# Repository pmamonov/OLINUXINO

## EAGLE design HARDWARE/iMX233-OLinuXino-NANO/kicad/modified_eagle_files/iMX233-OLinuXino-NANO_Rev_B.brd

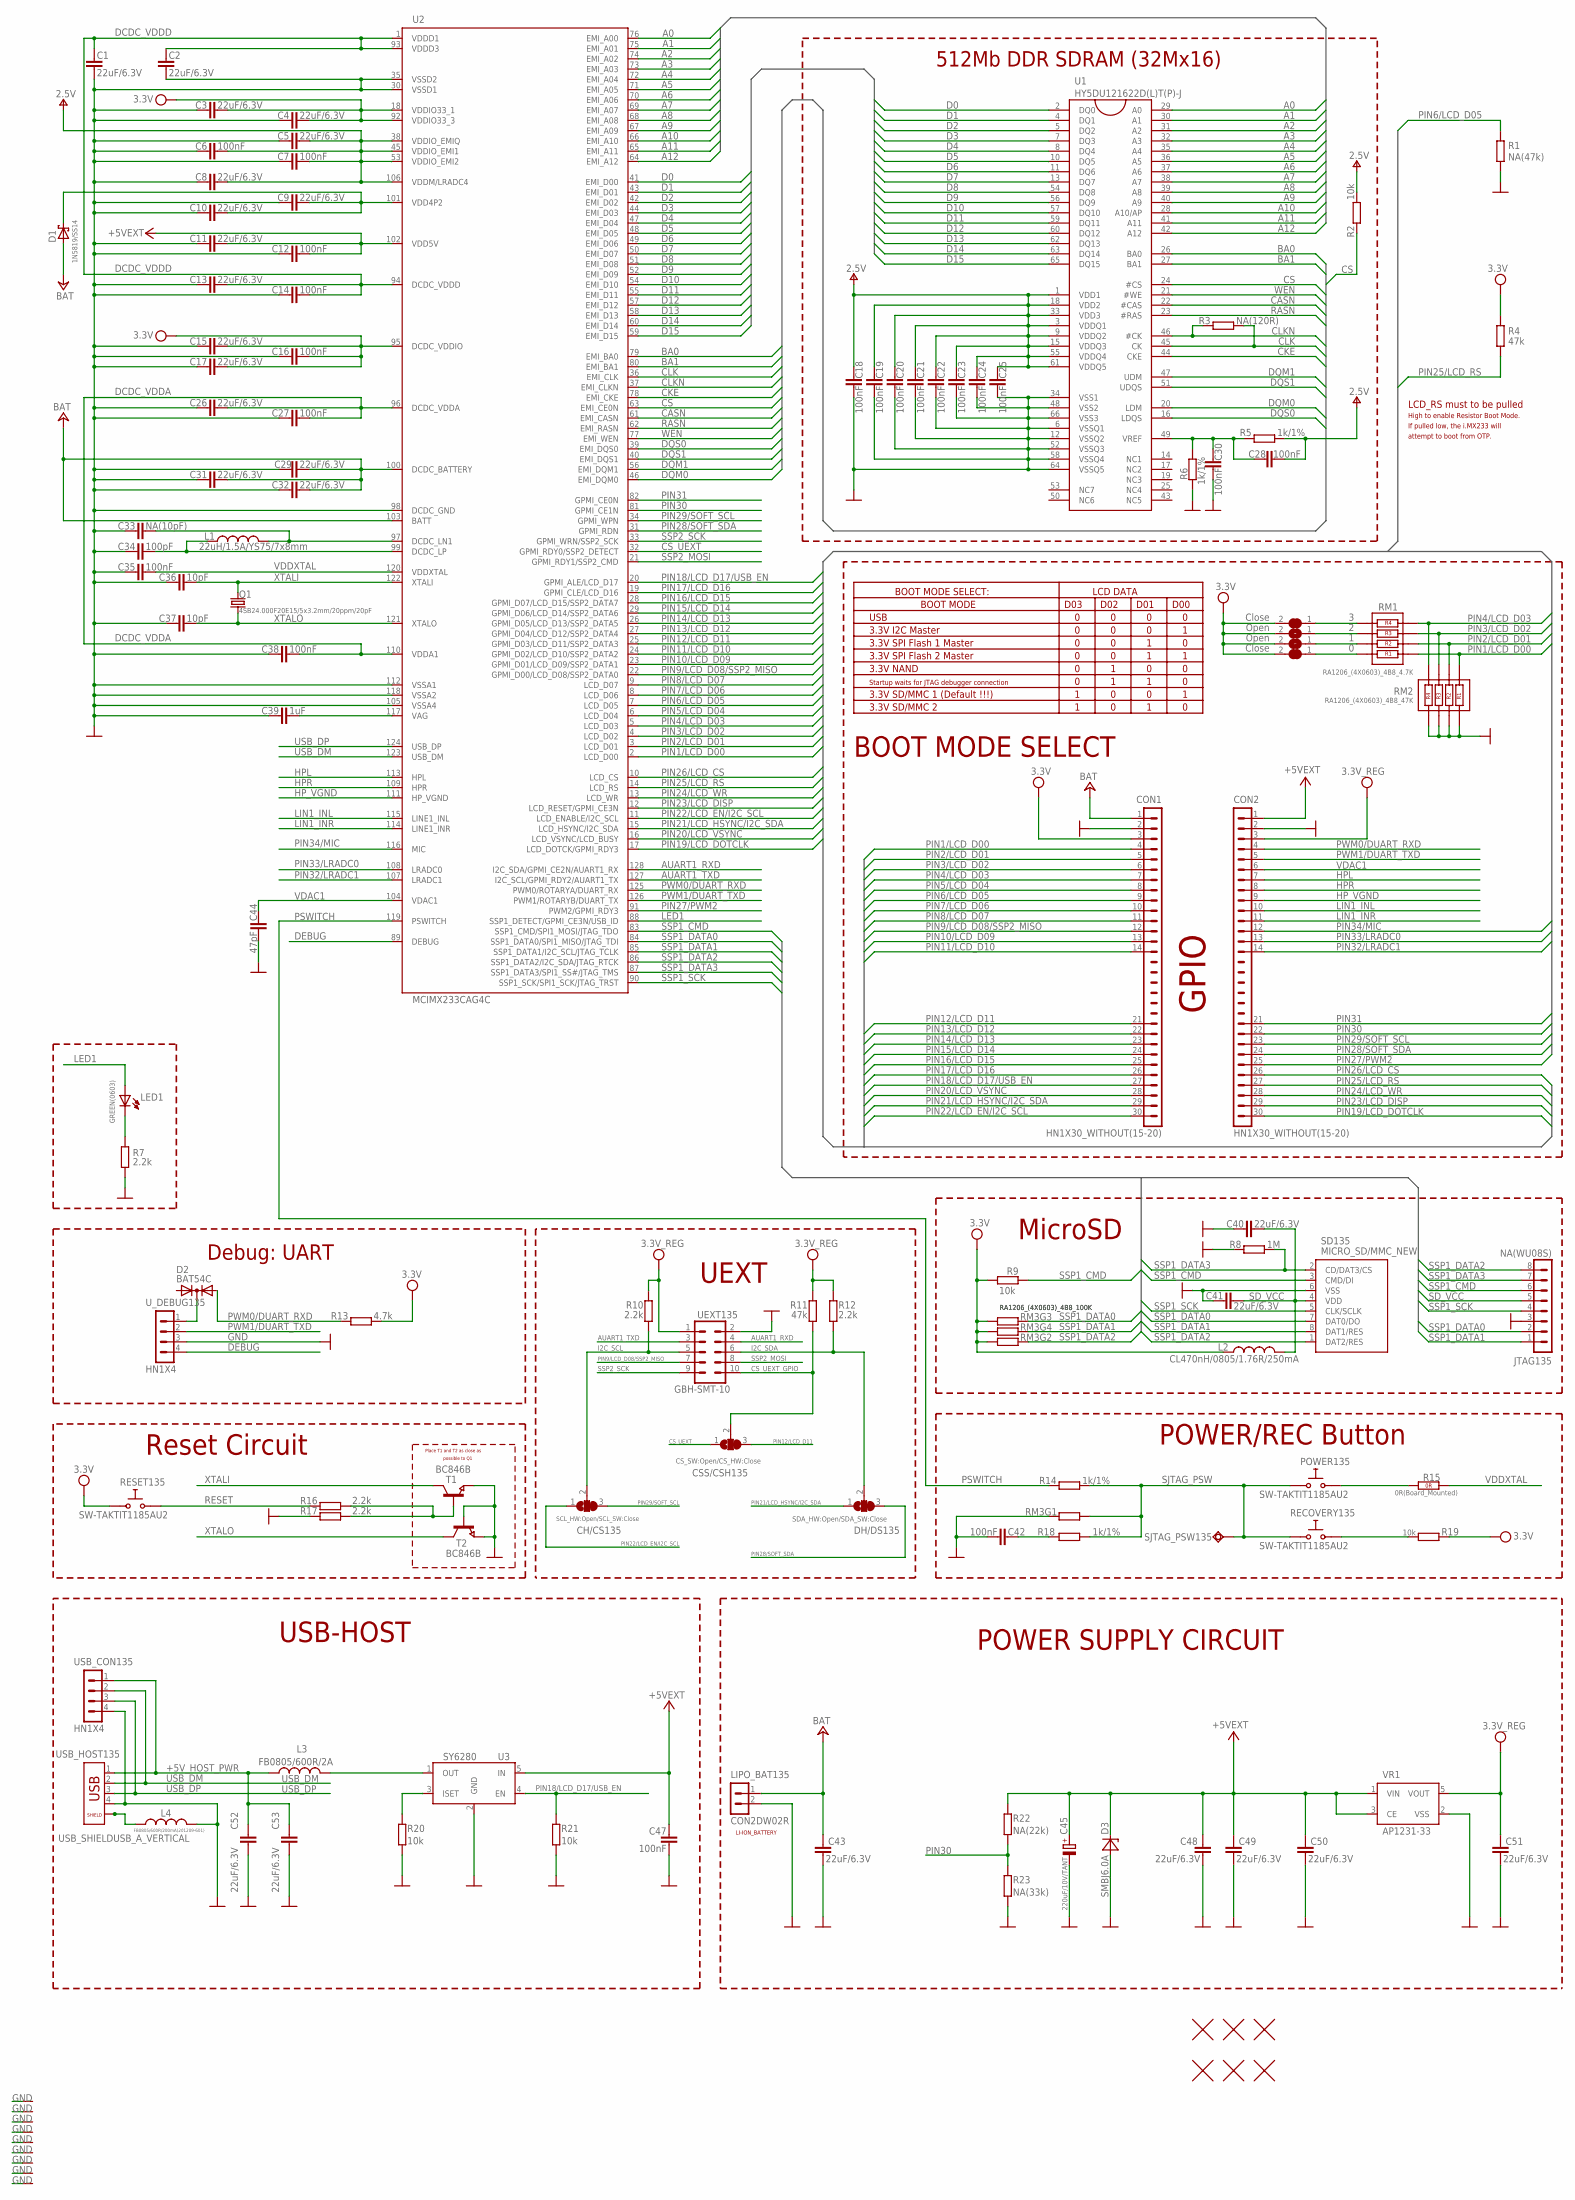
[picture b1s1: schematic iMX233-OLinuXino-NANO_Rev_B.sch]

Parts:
0, 3: Close; SJ_1_SMALLER
1, 2: Open; SJ_1_SMALLER
C1, C2, C3, C4, C5, C8, C9, C10, C11, C13, C15, C17, C26, C29, C31, C32, C40, C41, C43, C48, C49, C50, C51, C52, C53: 22uF/6.3V; C0603_DWS
C6, C7, C12, C14, C16, C18, C19, C20, C21, C22, C23, C24, C25, C27, C28, C30, C35, C38, C42: 100nF; C0402_TI
C33: NA(10pF); C0603_DWS
C34: 100pF; C0603_DWS
C36, C37: 10pF; C0603_DWS
C39: 1uF; C0603_DWS
C44: 47pF; C0603_DWS
C45: 220uF/10V/TANT; CT7343
C47: 100nF; C0603_DWS
CH/CS135: SCL_HW:Open/SCL_SW:Close; SJ_2_SMALLER
CON1, CON2: HN1X30_WITHOUT(15-20)
CSS/CSH135: CS_SW:Open/CS_HW:Close; SJ_2_SMALLER
D1: 1N5819/SS14; MLL-41
D2: BAT54C; SOT23C
D3: SMBJ6.0A; DO214AA
DH/DS135: SDA_HW:Open/SDA_SW:Close; SJ_2_SMALLER
JTAG135: NA(WU08S); WU08S
L1: 22uH/1.5A/YS75/7x8mm; L7078
L2: CL470nH/0805/1.76R/250mA; L0805_5MIL_DWS
L3: FB0805/600R/2A; L0805_5MIL_DWS
L4: FB0805/600R/200mA(201209-601); L0805_5MIL_DWS
LED1: GREEN(0603); LED-0603
LIPO_BAT135: CON2DW02R; DW02R
POWER135: SW-TAKTIT1185AU2; IT1185AU2
Q1: 4SB24.000F20E15/5x3.2mm/20ppm/20pF; HCX-4S
R1: NA(47k); R0603_5MIL_DWS
R2, R9, R19, R20, R21: 10k; R0603_5MIL_DWS
R3: NA(120R); R0603_5MIL_DWS
R4, R11: 47k; R0603_5MIL_DWS
R5, R6, R14, R18: 1k/1%; R0603_5MIL_DWS
R7, R10, R12, R16, R17: 2.2k; R0603_5MIL_DWS
R8: 1M; R0603_5MIL_DWS
R13: 4.7k; R0603_5MIL_DWS
R15: 0R(Board_Mounted); 0603_0R
R22: NA(22k); R0603_5MIL_DWS
R23: NA(33k); R0603_5MIL_DWS
RECOVERY135: SW-TAKTIT1185AU2; IT1185AU2
RESET135: SW-TAKTIT1185AU2; IT1185AU2
RM1: RA1206_(4X0603)_4B8_4.7K; R_MATRIX_4
RM2: RA1206_(4X0603)_4B8_47K; R_MATRIX_4
RM3: RA1206_(4X0603)_4B8_100K; R_MATRIX_4
SD135: MICRO_SD/MMC_NEW; TFR/C-MEM-CON
SJTAG_PSW135: TESTPAD40/70; TESTPAD
T1, T2: BC846B; SOT23
U1: HY5DU121622D(L)T(P)-J; 66TSOP-II
U2: MCIMX233CAG4C; TQFP128LD
U3: SY6280; SOT23-5
U$1, U$2, U$3, U$7, U$13, U$14: FIDUCIAL1X2; FIDUCIAL-1X2
UEXT135: GBH-SMT-10; ML10_S
USB_CON135: HN1X4
USB_HOST135: USB_SHIELDUSB_A_VERTICAL; USB_A_VERTICAL_PTH
U_DEBUG135: HN1X4
VP_0: VPDEV0; VPAC0
VP_1, VP_2, VP_3, VP_4, VP_5, VP_6, VP_7, VP_8: VPDEV1; VPAC1
VR1: AP1231-33; SOT-23-5

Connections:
+5V: C11.2, C12.2, C45.+, C47.1, C48.1, C49.1, C50.1, CON2.1, D3.C, R22.2, U2.102 (VDD5V), U3.5 (IN), VR1.1 (VIN), VR1.3 (CE)
+5V_HOST_PWR: C52.1, C53.1, L3.1, USB_CON135.1, USB_HOST135.1
+24V: C29.2, C31.2, C32.2, C43.1, CON1.1, D1.A, LIPO_BAT135.1, U2.100 (DCDC_BATTERY), U2.103 (BATT)
A0: U1.29 (A0), U2.76 (EMI_A00)
A1: U1.30 (A1), U2.75 (EMI_A01)
A2: U1.31 (A2), U2.74 (EMI_A02)
A3: U1.32 (A3), U2.73 (EMI_A03)
A4: U1.35 (A4), U2.72 (EMI_A04)
A5: U1.36 (A5), U2.71 (EMI_A05)
A6: U1.37 (A6), U2.70 (EMI_A06)
A7: U1.38 (A7), U2.69 (EMI_A07)
A8: U1.39 (A8), U2.68 (EMI_A08)
A9: U1.40 (A9), U2.67 (EMI_A09)
A10: U1.28 (A10/AP), U2.66 (EMI_A10)
A11: U1.41 (A11), U2.65 (EMI_A11)
A12: U1.42 (A12), U2.64 (EMI_A12)
AUART1_RXD: U2.128 (I2C_SDA/GPMI_CE2N/AUART1_RX), UEXT135.4
AUART1_TXD: U2.127 (I2C_SCL/GPMI_RDY2/AUART1_TX), UEXT135.3
BA0: U1.26 (BA0), U2.79 (EMI_BA0)
BA1: U1.27 (BA1), U2.80 (EMI_BA1)
CASN: U1.22 (#CAS), U2.61 (EMI_CASN)
CKE: U1.44 (CKE), U2.78 (EMI_CKE)
CLK: R3.2, U1.45 (CK), U2.36 (EMI_CLK)
CLKN: R3.1, U1.46 (#CK), U2.37 (EMI_CLKN)
CS: R2.1, U1.24 (#CS), U2.63 (EMI_CE0N)
CS_UEXT: CSS/CSH135.1, U2.32 (GPMI_RDY0/SSP2_DETECT)
CS_UEXT_GPIO: CSS/CSH135.2, R11.1, UEXT135.10
D0: U1.2 (DQ0), U2.41 (EMI_D00)
D1: U1.4 (DQ1), U2.43 (EMI_D01)
D2: U1.5 (DQ2), U2.42 (EMI_D02)
D3: U1.7 (DQ3), U2.44 (EMI_D03)
D4: U1.8 (DQ4), U2.47 (EMI_D04)
D5: U1.10 (DQ5), U2.48 (EMI_D05)
D6: U1.11 (DQ6), U2.49 (EMI_D06)
D7: U1.13 (DQ7), U2.50 (EMI_D07)
D8: U1.54 (DQ8), U2.51 (EMI_D08)
D9: U1.56 (DQ9), U2.52 (EMI_D09)
D10: U1.57 (DQ10), U2.54 (EMI_D10)
D11: U1.59 (DQ11), U2.55 (EMI_D11)
D12: U1.60 (DQ12), U2.57 (EMI_D12)
D13: U1.62 (DQ13), U2.58 (EMI_D13)
D14: U1.63 (DQ14), U2.60 (EMI_D14)
D15: U1.65 (DQ15), U2.59 (EMI_D15)
DCDC_VDDA: C26.2, C27.2, C38.2, U2.96 (DCDC_VDDA), U2.110 (VDDA1)
DCDC_VDDD: C1.2, C2.2, C13.2, C14.2, U2.1 (VDDD1), U2.93 (VDDD3), U2.94 (DCDC_VDDD)
DEBUG: U2.89 (DEBUG), U_DEBUG135.4
DQM0: U1.20 (LDM), U2.46 (EMI_DQM0)
DQM1: U1.47 (UDM), U2.56 (EMI_DQM1)
DQS0: U1.16 (LDQS), U2.39 (EMI_DQS0)
DQS1: U1.51 (UDQS), U2.40 (EMI_DQS1)
GND: C1.1, C2.1, C3.1, C4.1, C5.1, C6.1, C7.1, C8.1, C9.1, C10.1, C11.1, C12.1, C13.1, C14.1, C15.1, C16.1, C17.1, C18.1, C19.1, C20.1, C21.1, C22.1, C23.1, C24.1, C25.1, C26.1, C27.1, C29.1, C30.1, C31.1, C32.1, C33.1, C34.1, C35.1, C36.1, C37.1, C38.1, C39.1, C40.1, C41.1, C42.2, C43.2, C44.2, C45.-, C47.2, C48.2, C49.2, C50.2, C51.2, C52.2, C53.2, CON1.2, CON2.2, D3.A, JTAG135.3, L4.1, LIPO_BAT135.2, R1.1, R6.1, R7.1, R8.2, R17.2, R20.1, R21.1, R23.1, RM2.1.2, RM2.2.2, RM2.3.2, RM2.4.2, RM3.1.1 (1), SD135.6 (VSS), T1.2 (E), T2.1 (B), T2.2 (E), U1.6 (VSSQ1), U1.12 (VSSQ2), U1.34 (VSS1), U1.48 (VSS2), U1.52 (VSSQ3), U1.58 (VSSQ4), U1.64 (VSSQ5), U1.66 (VSS3), U2.30 (VSSD1), U2.35 (VSSD2), U2.98 (DCDC_GND), U2.105 (VSSA4), U2.112 (VSSA1), U2.118 (VSSA2), U3.2 (GND), UEXT135.2, USB_CON135.4, USB_HOST135.4, U_DEBUG135.3, VP_0.VP, VP_1.VP, VP_2.VP, VP_3.VP, VP_4.VP, VP_5.VP, VP_6.VP, VP_7.VP, VP_8.VP, VR1.2 (VSS)
HPL: CON2.7, U2.113 (HPL)
HPR: CON2.8, U2.109 (HPR)
HP_VGND: CON2.9, U2.111 (HP_VGND)
I2C_SCL: CH/CS135.2, R10.1, UEXT135.5
I2C_SDA: DH/DS135.2, R12.1, UEXT135.6
LED1: LED1.A, U2.88 (SSP1_DETECT/GPMI_CE3N/USB_ID)
LIN1_INL: CON2.10, U2.115 (LINE1_INL)
LIN1_INR: CON2.11, U2.114 (LINE1_INR)
unnamed: POWER135.1 (0), R15.1 (1.1)
unnamed: L3.2, U3.1 (OUT)
unnamed: R20.2, U3.3 (ISET)
unnamed: C28.2, C30.2, R5.1, R6.2, U1.49 (VREF)
unnamed: R19.1, RECOVERY135.1 (0)
unnamed: D2.3 (K), U_DEBUG135.1
unnamed: C33.2, L1.2, U2.97 (DCDC_LN1)
unnamed: C34.2, L1.1, U2.99 (DCDC_LP)
unnamed: C39.2, U2.117 (VAG)
unnamed: C42.1, R18.1
unnamed: LED1.C, R7.2
unnamed: R16.1, R17.1, T1.1 (B)
unnamed: 3.1, RM1.4.1
unnamed: 2.1, RM1.3.1
unnamed: 1.1, RM1.2.1
unnamed: 0.1, RM1.1.1
unnamed: L4.2, USB_HOST135.P$3 (5), USB_HOST135.P$4 (6)
PIN1/LCD_D00: CON1.4, RM1.1.2, RM2.1.1, U2.2 (LCD_D00)
PIN2/LCD_D01: CON1.5, RM1.2.2, RM2.2.1, U2.3 (LCD_D01)
PIN3/LCD_D02: CON1.6, RM1.3.2, RM2.3.1, U2.4 (LCD_D02)
PIN4/LCD_D03: CON1.7, RM1.4.2, RM2.4.1, U2.5 (LCD_D03)
PIN5/LCD_D04: CON1.8, U2.6 (LCD_D04)
PIN6/LCD_D05: CON1.9, R1.2, U2.7 (LCD_D05)
PIN7/LCD_D06: CON1.10, U2.8 (LCD_D06)
PIN8/LCD_D07: CON1.11, U2.9 (LCD_D07)
PIN9/LCD_D08/SSP2_MISO: CON1.12, U2.22 (GPMI_D00/LCD_D08/SSP2_DATA0), UEXT135.7
PIN10/LCD_D09: CON1.13, U2.23 (GPMI_D01/LCD_D09/SSP2_DATA1)
PIN11/LCD_D10: CON1.14, U2.24 (GPMI_D02/LCD_D10/SSP2_DATA2)
PIN12/LCD_D11: CON1.21, CSS/CSH135.3, U2.25 (GPMI_D03/LCD_D11/SSP2_DATA3)
PIN13/LCD_D12: CON1.22, U2.27 (GPMI_D04/LCD_D12/SSP2_DATA4)
PIN14/LCD_D13: CON1.23, U2.26 (GPMI_D05/LCD_D13/SSP2_DATA5)
PIN15/LCD_D14: CON1.24, U2.29 (GPMI_D06/LCD_D14/SSP2_DATA6)
PIN16/LCD_D15: CON1.25, U2.28 (GPMI_D07/LCD_D15/SSP2_DATA7)
PIN17/LCD_D16: CON1.26, U2.19 (GPMI_CLE/LCD_D16)
PIN18/LCD_D17/USB_EN: CON1.27, R21.2, U2.20 (GPMI_ALE/LCD_D17), U3.4 (EN)
PIN19/LCD_DOTCLK: CON2.30, U2.17 (LCD_DOTCK/GPMI_RDY3)
PIN20/LCD_VSYNC: CON1.28, U2.16 (LCD_VSYNC/LCD_BUSY)
PIN21/LCD_HSYNC/I2C_SDA: CON1.29, DH/DS135.1, U2.15 (LCD_HSYNC/I2C_SDA)
PIN22/LCD_EN/I2C_SCL: CH/CS135.1, CON1.30, U2.11 (LCD_ENABLE/I2C_SCL)
PIN23/LCD_DISP: CON2.29, U2.12 (LCD_RESET/GPMI_CE3N)
PIN24/LCD_WR: CON2.28, U2.13 (LCD_WR)
PIN25/LCD_RS: CON2.27, R4.2, U2.14 (LCD_RS)
PIN26/LCD_CS: CON2.26, U2.10 (LCD_CS)
PIN27/PWM2: CON2.25, U2.91 (PWM2/GPMI_RDY3)
PIN28/SOFT_SDA: CON2.24, DH/DS135.3, U2.31 (GPMI_RDN)
PIN29/SOFT_SCL: CH/CS135.3, CON2.23, U2.34 (GPMI_WPN)
PIN30: CON2.22, R22.1, R23.2, U2.81 (GPMI_CE1N)
PIN31: CON2.21, U2.82 (GPMI_CE0N)
PIN32/LRADC1: CON2.14, U2.107 (LRADC1)
PIN33/LRADC0: CON2.13, U2.108 (LRADC0)
PIN34/MIC: CON2.12, U2.116 (MIC)
PSWITCH: R14.1, U2.119 (PSWITCH)
PWM0/DUART_RXD: CON2.4, D2.2 (A2), R13.2, U2.125 (PWM0/ROTARYA/DUART_RX)
PWM1/DUART_TXD: CON2.5, U2.126 (PWM1/ROTARYB/DUART_TX), U_DEBUG135.2
RASN: U1.23 (#RAS), U2.62 (EMI_RASN)
RESET: R16.2, RESET135.1 (0)
SD_VCC: C40.2, C41.2, JTAG135.5, L2.2, SD135.4 (VDD)
SJTAG_PSW: POWER135.2 (1), R14.2, R18.2, RECOVERY135.2 (1), RM3.1.2 (2), SJTAG_PSW135.P$1
SSP1_CMD: JTAG135.6, R9.1, SD135.3 (CMD/DI), U2.83 (SSP1_CMD/SPI1_MOSI/JTAG_TDO)
SSP1_DATA0: JTAG135.2, RM3.3.2 (2), SD135.7 (DAT0/DO), U2.84 (SSP1_DATA0/SPI1_MISO/JTAG_TDI)
SSP1_DATA1: JTAG135.1, RM3.4.2 (2), SD135.8 (DAT1/RES), U2.85 (SSP1_DATA1/I2C_SCL/JTAG_TCLK)
SSP1_DATA2: JTAG135.8, RM3.2.2 (2), SD135.1 (DAT2/RES), U2.86 (SSP1_DATA2/I2C_SDA/JTAG_RTCK)
SSP1_DATA3: JTAG135.7, R8.1, SD135.2 (CD/DAT3/CS), U2.87 (SSP1_DATA3/SPI1_SS#/JTAG_TMS)
SSP1_SCK: JTAG135.4, SD135.5 (CLK/SCLK), U2.90 (SSP1_SCK/SPI1_SCK/JTAG_TRST)
SSP2_MOSI: U2.21 (GPMI_RDY1/SSP2_CMD), UEXT135.8
SSP2_SCK: U2.33 (GPMI_WRN/SSP2_SCK), UEXT135.9
USB_DM: U2.123 (USB_DM), USB_CON135.2, USB_HOST135.2
USB_DP: U2.124 (USB_DP), USB_CON135.3, USB_HOST135.3
V+: C5.2, C6.2, C7.2, C8.2, C18.2, C19.2, C20.2, C21.2, C22.2, C23.2, C24.2, C25.2, C28.1, R2.2, R5.2, U1.1 (VDD1), U1.3 (VDDQ1), U1.9 (VDDQ2), U1.15 (VDDQ3), U1.18 (VDD2), U1.33 (VDD3), U1.55 (VDDQ4), U1.61 (VDDQ5), U2.38 (VDDIO_EMIQ), U2.45 (VDDIO_EMI1), U2.53 (VDDIO_EMI2), U2.106 (VDDM/LRADC4)
VCC: 0.2, 1.2, 2.2, 3.2, C3.2, C4.2, C15.2, C16.2, C17.2, CON1.3, L2.1, R4.1, R9.2, R13.1, R19.2, RESET135.2 (1), RM3.2.1 (1), RM3.3.1 (1), RM3.4.1 (1), U2.18 (VDDIO33_1), U2.92 (VDDIO33_3), U2.95 (DCDC_VDDIO)
VDAC1: C44.1, CON2.6, U2.104 (VDAC1)
VDD4P2: C9.2, C10.2, D1.K (C), U2.101 (VDD4P2)
VDDXTAL: C35.2, R15.2 (1.2), U2.120 (VDDXTAL)
VPP: C51.1, CON2.3, R10.2, R11.2, R12.2, UEXT135.1, VR1.5 (VOUT)
WEN: U1.21 (#WE), U2.77 (EMI_WEN)
XTALI: C36.2, Q1.2, T1.3 (C), U2.122 (XTALI)
XTALO: C37.2, Q1.1, T2.3 (C), U2.121 (XTALO)

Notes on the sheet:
POWER SUPPLY CIRCUIT
Place T1 and T2 as close as
possible to Q1
Reset Circuit
512Mb DDR SDRAM (32Mx16)
MicroSD
POWER/REC Button
BOOT MODE SELECT
BOOT MODE SELECT:
LCD DATA
BOOT MODE
D03
D02
D01
D00
USB
3.3V I2C Master
3.3V SPI Flash 1 Master
3.3V SPI Flash 2 Master
3.3V NAND
Startup waits for JTAG debugger connection
3.3V SD/MMC 1 (Default !!!)
3.3V SD/MMC 2
LCD_RS must to be pulled
High to enable Resistor Boot Mode.
If pulled low, the i.MX233 will
attempt to boot from OTP.
GPIO
Debug: UART
UEXT
USB-HOST
LI-ION_BATTERY

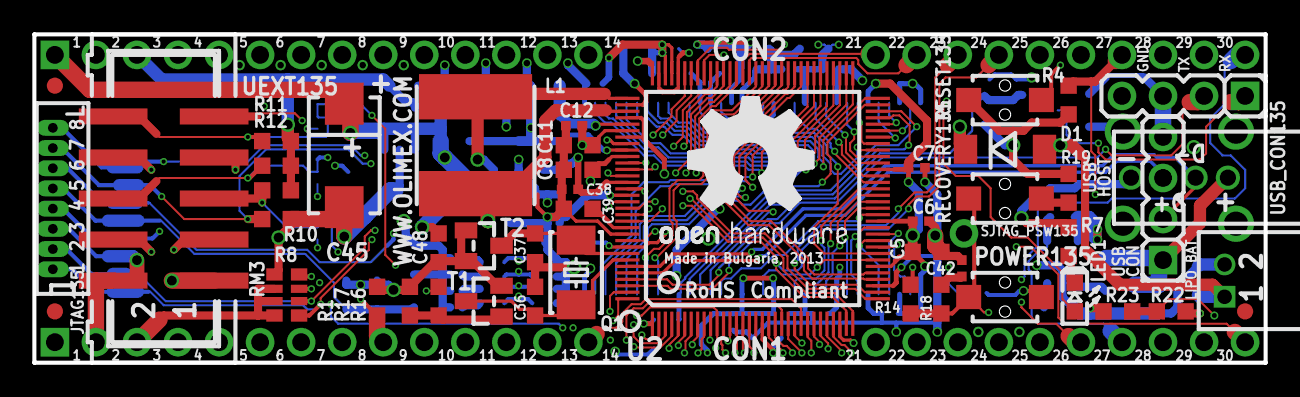
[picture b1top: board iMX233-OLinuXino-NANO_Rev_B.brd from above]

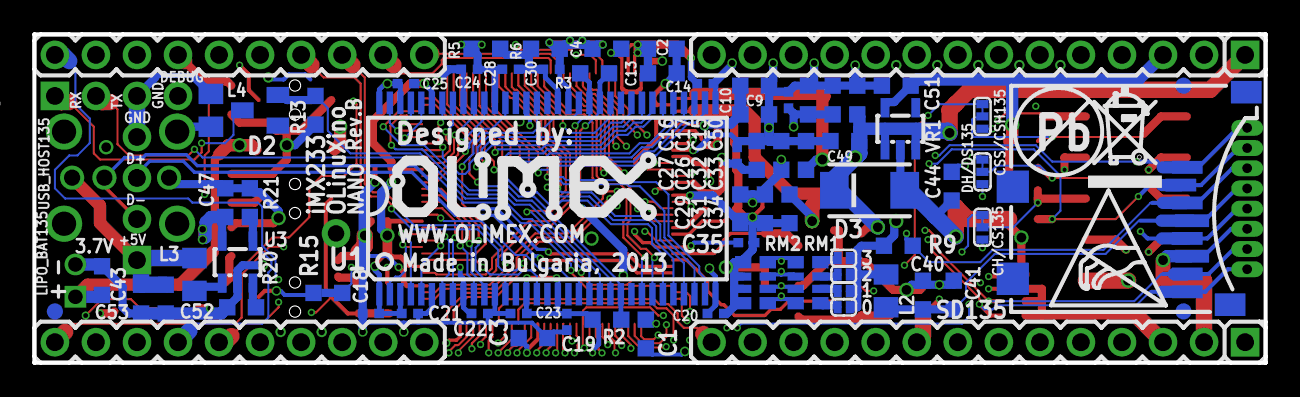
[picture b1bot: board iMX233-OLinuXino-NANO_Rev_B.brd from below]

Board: 6 copper layers, 76.2 x 20.3 mm, 133 parts (75 on the bottom side), 136 nets.

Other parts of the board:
U$4: ESD_SYMBOL
U$6: RECYCLE_BIN1/8
U$8: OLIMEX1_V
U$15: PB
U$18: LOGO-OPENHARDWARE_8X8

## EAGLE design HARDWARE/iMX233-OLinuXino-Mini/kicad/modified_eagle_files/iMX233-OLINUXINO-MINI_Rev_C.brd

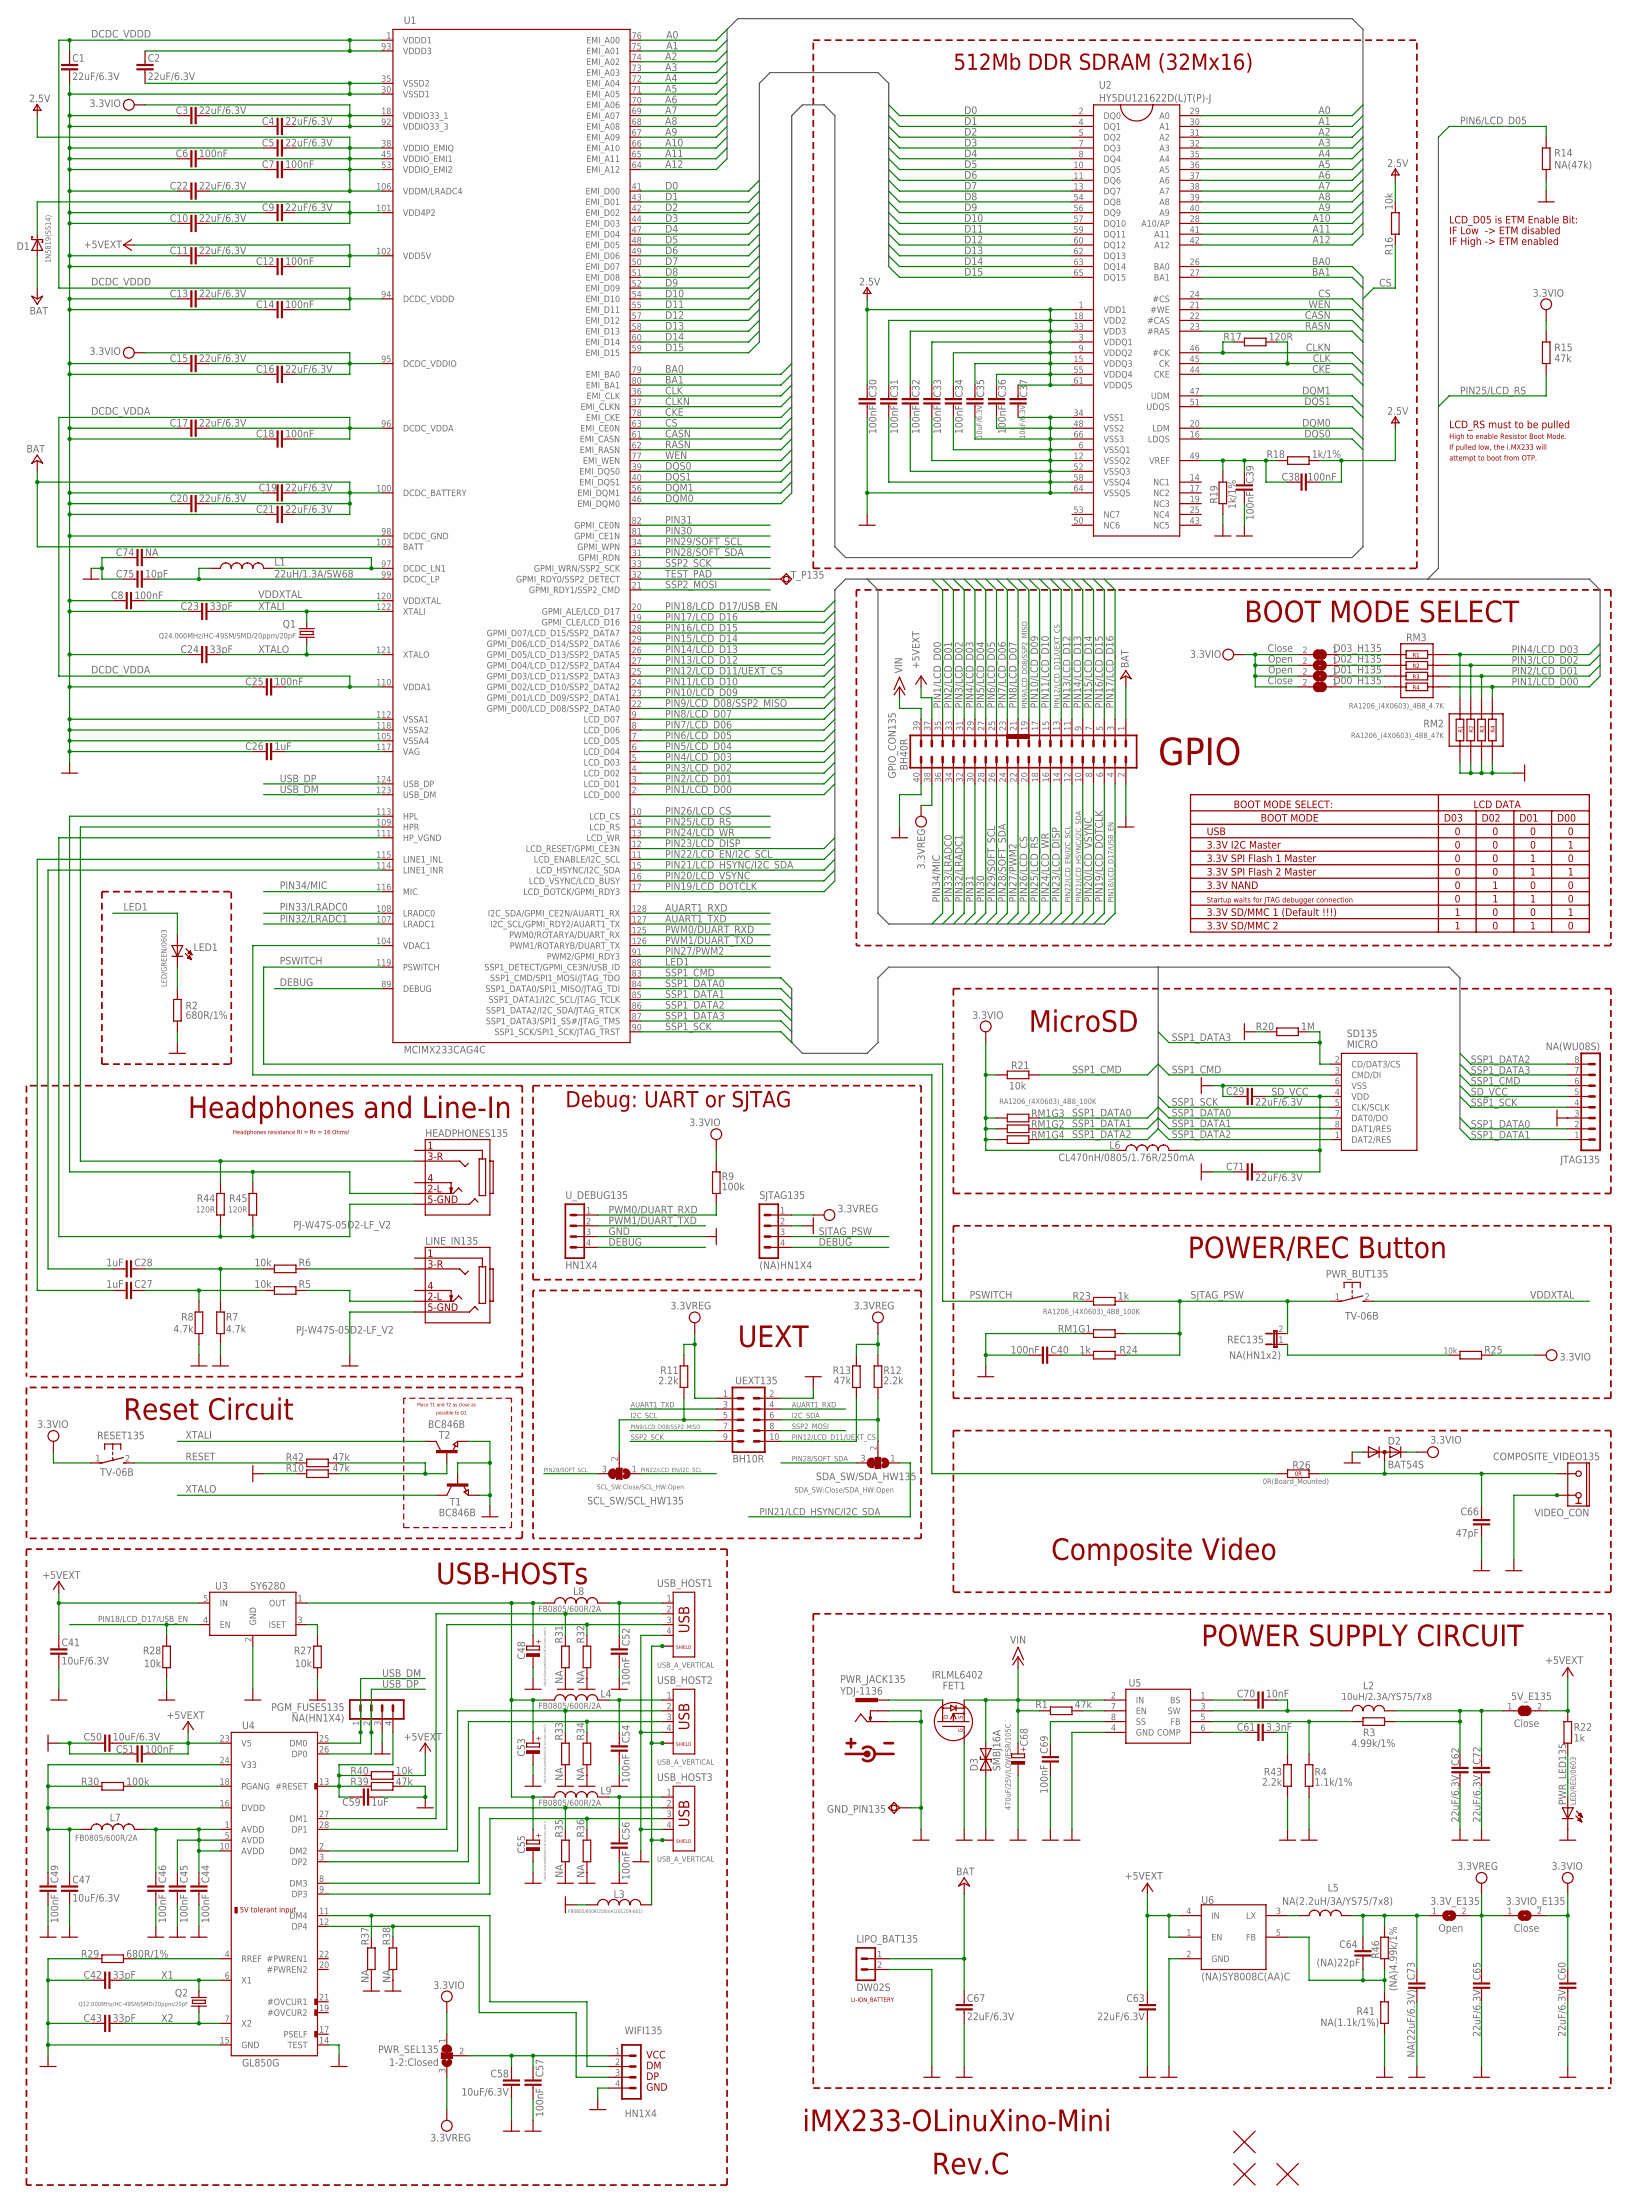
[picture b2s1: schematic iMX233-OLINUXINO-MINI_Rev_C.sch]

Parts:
3.3VIO_E135: Close; SJ_1_SMALLER
3.3V_E135: Open; SJ_1_SMALLER
5V_E135: Close; SJ_1_SMALLER_CLOSE
C1, C2, C3, C4, C5, C9, C10, C11, C13, C15, C16, C17, C19, C20, C21, C22, C29, C60, C62, C63, C65, C67, C71, C72: 22uF/6.3V; C0805_5MIL_DWS
C6, C7, C8, C12, C14, C18, C25, C30, C31, C32, C33, C34, C36, C38, C39, C40, C44, C45, C46, C49, C51, C52, C54, C56, C57, C69: 100nF; C0603_DWS
C23, C24, C42, C43: 33pF; C0603_DWS
C26, C27, C28, C59: 1uF; C0603_DWS
C35, C37, C41, C47, C50, C58: 10uF/6.3V; C0603_DWS
C48, C53, C55: 100uF/16V/LOWESR/105C/6.3x11mm_RM2.5; E2,5-6,3
C61: 3.3nF; C0603_DWS
C64: (NA)22pF; C0603_DWS
C66: 47pF; C0603_DWS
C68: 470uF/25V/LOWESR/105C; E5-10,5
C70: 10nF; C0603_DWS
C73: NA(22uF/6.3V); C0805_5MIL_DWS
C74: NA; C0603_DWS
C75: 10pF; C0603_DWS
COMPOSITE_VIDEO135: VIDEO_CON
D00_H135, D03_H135: Close; SJ_1_SMALLER
D1: 1N5819(SS14); MLL-41
D01_H135, D02_H135: Open; SJ_1_SMALLER
D2: BAT54S; SOT23C(BAT54S)
D3: SMBJ16A; DO214AA
FET1: IRLML6402; SOT23
GND_PIN135: TESTPAD3; TEST_PAD40/70/SQUARE
GPIO_CON135: BH40R
HEADPHONES135: PJ-W47S-05D2-LF_V2; PJ-W47S-05D2-LF_5PIN_V2
JTAG135: NA(WU08S); WU08S
L1: 22uH/1.3A/SW68; CD53
L2: 10uH/2.3A/YS75/7x8; 8X8MM_3131
L3: FB0805/600R/200mA(201209-601); L0805_5MIL_DWS
L4, L7, L8, L9: FB0805/600R/2A; L0805_5MIL_DWS
L5: NA(2.2uH/3A/YS75/7x8); 8X8MM_3131
L6: CL470nH/0805/1.76R/250mA; L0805_5MIL_DWS
LED1: LED/GREEN/0603; LED-0603
LINE_IN135: PJ-W47S-05D2-LF_V2; PJ-W47S-05D2-LF_5PIN_V2
LIPO_BAT135: DW02S
PGM_FUSES135: NA(HN1X4); HN1X4
PWR_BUT135: TV-06B; B3F-31XX
PWR_JACK135: YDJ-1136; PWR_JACK_UNI_MILLING
PWR_LED135: LED/RED/0603; LED-0603
PWR_SEL135: 1-2:Closed; SJ_2_SMALL
Q1: Q24.000MHz/HC-49SM/SMD/20ppm/20pF; HC49/SMD2_THIN
Q2: Q12.000MHz/HC-49SM/SMD/20ppm/20pF; HC49/SMD2_THIN
R1, R10, R13, R15, R39, R42: 47k; R0603_5MIL_DWS
R2, R29: 680R/1%; R0603_5MIL_DWS
R3: 4.99k/1%; R0603_5MIL_DWS
R4: 1.1k/1%; R0603_5MIL_DWS
R5, R6, R16, R21, R27, R28, R40: 10k; R0603_5MIL_DWS
R7, R8: 4.7k; R0603_5MIL_DWS
R9, R30: 100k; R0603_5MIL_DWS
R11, R12, R43: 2.2k; R0603_5MIL_DWS
R14: NA(47k); R0603_5MIL_DWS
R17, R44, R45: 120R; R0603_5MIL_DWS
R18, R19: 1k/1%; R0603_5MIL_DWS
R20: 1M; R0603_5MIL_DWS
R22, R23, R24: 1k; R0603_5MIL_DWS
R25: 10k; R0603_5MIL_DWS_NA
R26: 0R(Board_Mounted); 0603_0R
R31, R32, R33, R34, R35, R36, R37, R38: NA; R0603_5MIL_DWS
R41: NA(1.1k/1%); R0603_5MIL_DWS
R46: (NA)4.99k/1%; R0603_5MIL_DWS
REC135: NA(HN1x2); JP1
RESET135: TV-06B; B3F-31XX
RM1: RA1206_(4X0603)_4B8_100K; R_MATRIX_4
RM2: RA1206_(4X0603)_4B8_47K; R_MATRIX_4
RM3: RA1206_(4X0603)_4B8_4.7K; R_MATRIX_4
SCL_SW/SCL_HW135: SCL_SW:Close/SCL_HW:Open; SJ_2_SMALLER
SD135: MICRO; TFR-MEM-CON
SDA_SW/SDA_HW135: SDA_SW:Close/SDA_HW:Open; SJ_2_SMALLER
SJTAG135: (NA)HN1X4; HN1X4
T1, T2: BC846B; SOT23
T_P135: TESTPAD50/40; SMD50/40
U1: MCIMX233CAG4C; TQFP128LD
U2: HY5DU121622D(L)T(P)-J; 66TSOP-II
U3: SY6280; SOT23-5
U4: GL850G; SSOP28
U5: MP1482DS; SOIC8
U6: (NA)SY8008C(AA)C; SOT23-5
U$1, U$2, U$3: FIDUCIAL1X2; FIDUCIAL-1X2
UEXT135: BH10R
USB_HOST1, USB_HOST2, USB_HOST3: USB_A_VERTICAL; USB_A_VERTICAL_PTH
U_DEBUG135: HN1X4
WIFI135: HN1X4

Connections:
+5V: 5V_E135.2, C11.2, C12.2, C41.1, C50.1, C51.1, C63.1, GPIO_CON135.37, R22.1, R40.2, U1.102 (VDD5V), U3.5 (IN), U4.23 (V5), U6.1 (EN), U6.4 (IN)
+15V: C68.+, D3.C (2), FET1.2 (S), GPIO_CON135.39, R1.1, U5.2 (IN)
+24V: C19.2, C20.2, C21.2, C67.2, D1.A, GPIO_CON135.1, LIPO_BAT135.1, U1.100 (DCDC_BATTERY), U1.103 (BATT)
A0: U1.76 (EMI_A00), U2.29 (A0)
A1: U1.75 (EMI_A01), U2.30 (A1)
A2: U1.74 (EMI_A02), U2.31 (A2)
A3: U1.73 (EMI_A03), U2.32 (A3)
A4: U1.72 (EMI_A04), U2.35 (A4)
A5: U1.71 (EMI_A05), U2.36 (A5)
A6: U1.70 (EMI_A06), U2.37 (A6)
A7: U1.69 (EMI_A07), U2.38 (A7)
A8: U1.68 (EMI_A08), U2.39 (A8)
A9: U1.67 (EMI_A09), U2.40 (A9)
A10: U1.66 (EMI_A10), U2.28 (A10/AP)
A11: U1.65 (EMI_A11), U2.41 (A11)
A12: U1.64 (EMI_A12), U2.42 (A12)
AUART1_RXD: U1.128 (I2C_SDA/GPMI_CE2N/AUART1_RX), UEXT135.4
AUART1_TXD: U1.127 (I2C_SCL/GPMI_RDY2/AUART1_TX), UEXT135.3
BA0: U1.79 (EMI_BA0), U2.26 (BA0)
BA1: U1.80 (EMI_BA1), U2.27 (BA1)
CASN: U1.61 (EMI_CASN), U2.22 (#CAS)
CKE: U1.78 (EMI_CKE), U2.44 (CKE)
CLK: R17.2, U1.36 (EMI_CLK), U2.45 (CK)
CLKN: R17.1, U1.37 (EMI_CLKN), U2.46 (#CK)
CS: R16.1, U1.63 (EMI_CE0N), U2.24 (#CS)
D0: U1.41 (EMI_D00), U2.2 (DQ0)
D1: U1.43 (EMI_D01), U2.4 (DQ1)
D2: U1.42 (EMI_D02), U2.5 (DQ2)
D3: U1.44 (EMI_D03), U2.7 (DQ3)
D4: U1.47 (EMI_D04), U2.8 (DQ4)
D5: U1.48 (EMI_D05), U2.10 (DQ5)
D6: U1.49 (EMI_D06), U2.11 (DQ6)
D7: U1.50 (EMI_D07), U2.13 (DQ7)
D8: U1.51 (EMI_D08), U2.54 (DQ8)
D9: U1.52 (EMI_D09), U2.56 (DQ9)
D10: U1.54 (EMI_D10), U2.57 (DQ10)
D11: U1.55 (EMI_D11), U2.59 (DQ11)
D12: U1.57 (EMI_D12), U2.60 (DQ12)
D13: U1.58 (EMI_D13), U2.62 (DQ13)
D14: U1.60 (EMI_D14), U2.63 (DQ14)
D15: U1.59 (EMI_D15), U2.65 (DQ15)
DCDC_VDDA: C17.2, C18.2, C25.2, U1.96 (DCDC_VDDA), U1.110 (VDDA1)
DCDC_VDDD: C1.2, C2.2, C13.2, C14.2, U1.1 (VDDD1), U1.93 (VDDD3), U1.94 (DCDC_VDDD)
DEBUG: SJTAG135.4, U1.89 (DEBUG), U_DEBUG135.4
DQM0: U1.46 (EMI_DQM0), U2.20 (LDM)
DQM1: U1.56 (EMI_DQM1), U2.47 (UDM)
DQS0: U1.39 (EMI_DQS0), U2.16 (LDQS)
DQS1: U1.40 (EMI_DQS1), U2.51 (UDQS)
GND: C1.1, C2.1, C3.1, C4.1, C5.1, C6.1, C7.1, C8.1, C9.1, C10.1, C11.1, C12.1, C13.1, C14.1, C15.1, C16.1, C17.1, C18.1, C19.1, C20.1, C21.1, C22.1, C23.1, C24.1, C25.1, C26.1, C29.1, C30.1, C31.1, C32.1, C33.1, C34.1, C35.1, C36.1, C37.1, C39.1, C40.2, C41.2, C42.1, C43.1, C44.2, C45.2, C46.2, C47.2, C48.-, C49.2, C50.2, C51.2, C52.2, C53.-, C54.2, C55.-, C56.2, C57.2, C58.2, C59.1, C60.2, C62.2, C63.2, C65.2, C66.2, C67.1, C68.-, C69.2, C71.1, C72.2, C73.2, C74.1, C75.1, COMPOSITE_VIDEO135.GND1 (GND), COMPOSITE_VIDEO135.GND2 (GND), COMPOSITE_VIDEO135.GND3 (GND), D2.1 (A), D3.A (1), FET1.1 (G), GND_PIN135.P$1, GPIO_CON135.2, GPIO_CON135.40, JTAG135.3, L3.1, LINE_IN135.5, LIPO_BAT135.2, PGM_FUSES135.3, PWR_JACK135.-, PWR_JACK135.--, PWR_LED135.C, R2.1, R4.2, R7.1, R8.1, R10.2, R14.1, R19.1, R20.2, R27.1, R28.1, R29.1, R31.1, R32.1, R33.1, R34.1, R35.1, R36.1, R37.1, R38.1, R39.2, R41.2, R43.2, RM1.1.1 (1), RM2.1.1, RM2.2.1, RM2.3.1, RM2.4.1, SD135.6 (VSS), SJTAG135.2, T1.1 (B), T1.2 (E), T2.2 (E), U1.30 (VSSD1), U1.35 (VSSD2), U1.98 (DCDC_GND), U1.105 (VSSA4), U1.112 (VSSA1), U1.118 (VSSA2), U2.6 (VSSQ1), U2.12 (VSSQ2), U2.34 (VSS1), U2.48 (VSS2), U2.52 (VSSQ3), U2.58 (VSSQ4), U2.64 (VSSQ5), U2.66 (VSS3), U3.2 (GND), U4.14 (TEST), U4.15 (GND), U5.4 (GND), U6.2 (GND), UEXT135.2, USB_HOST1.4, USB_HOST2.4, USB_HOST3.4, U_DEBUG135.3, WIFI135.4
HP_VGND: HEADPHONES135.5, R44.1, R45.1, U1.111 (HP_VGND)
I2C_SCL: R11.1, SCL_SW/SCL_HW135.2, UEXT135.5
I2C_SDA: R12.1, SDA_SW/SDA_HW135.2, UEXT135.6
LED1: LED1.A, U1.88 (SSP1_DETECT/GPMI_CE3N/USB_ID)
unnamed: R27.2, U3.3 (ISET)
unnamed: R29.2, U4.4 (RREF)
unnamed: R30.2, U4.18 (PGANG)
unnamed: C66.1, COMPOSITE_VIDEO135.IO, D2.3 (AK), R26.2 (1.2)
unnamed: C59.2, PGM_FUSES135.4, R39.1, R40.1, U4.13 (#RESET)
unnamed: LINE_IN135.2, R5.2
unnamed: C38.2, C39.2, R18.1, R19.2, U2.49 (VREF)
unnamed: R25.1, REC135.1
unnamed: R31.2, U4.27 (DM1), USB_HOST1.2
unnamed: C44.1, C45.1, C46.1, L7.2, U4.1 (AVDD), U4.5 (AVDD), U4.10 (AVDD)
unnamed: C47.1, C49.1, L7.1, R30.1, U4.16 (DVDD), U4.24 (V33)
unnamed: R32.2, U4.28 (DP1), USB_HOST1.3
unnamed: R33.2, U4.2 (DM2), USB_HOST2.2
unnamed: R34.2, U4.3 (DP2), USB_HOST2.3
unnamed: HEADPHONES135.2, R45.2, U1.113 (HPL)
unnamed: L3.2, USB_HOST1.P$3 (5), USB_HOST1.P$4 (6), USB_HOST2.P$3 (5), USB_HOST2.P$4 (6), USB_HOST3.P$3 (5), USB_HOST3.P$4 (6)
unnamed: C48.+, C53.+, C55.+, L4.1, L8.1, L9.1, U3.1 (OUT)
unnamed: C74.2, L1.2, U1.97 (DCDC_LN1)
unnamed: C75.2, L1.1, U1.99 (DCDC_LP)
unnamed: C52.1, L8.2, USB_HOST1.1
unnamed: HEADPHONES135.3, R44.2, U1.109 (HPR)
unnamed: C57.1, C58.1, PWR_SEL135.2, WIFI135.1
unnamed: 5V_E135.1, C62.1, C72.1, L2.2, R3.2
unnamed: C54.1, L4.2, USB_HOST2.1
unnamed: C26.2, U1.117 (VAG)
unnamed: R35.2, U4.8 (DM3), USB_HOST3.2
unnamed: C56.1, L9.2, USB_HOST3.1
unnamed: R36.2, U4.9 (DP3), USB_HOST3.3
unnamed: LINE_IN135.3, R6.2
unnamed: R37.2, U4.11 (DM4), WIFI135.2
unnamed: FET1.3 (D), PWR_JACK135.+
unnamed: C28.1, R6.1, R7.2
unnamed: C27.1, R5.1, R8.2
unnamed: C27.2, U1.115 (LINE1_INL)
unnamed: C28.2, U1.114 (LINE1_INR)
unnamed: C69.1, U5.8 (SS)
unnamed: R1.2, U5.7 (EN)
unnamed: C40.1, R24.1
unnamed: R38.2, U4.12 (DP4), WIFI135.3
unnamed: LED1.C, R2.2
unnamed: R10.1, R42.1, T2.1 (B)
unnamed: C70.1, U5.1 (BS)
unnamed: C70.2, L2.1, U5.3 (SW)
unnamed: C61.1, U5.6 (COMP)
unnamed: C61.2, R43.1
unnamed: R3.1, R4.1, U5.5 (FB)
unnamed: L5.1, U6.3 (LX)
unnamed: 3.3V_E135.1, C64.1, C73.1, L5.2, R46.1
unnamed: C64.2, R41.1, R46.2, U6.5 (FB)
unnamed: D03_H135.1, RM3.1.2
unnamed: D02_H135.1, RM3.2.2
unnamed: D01_H135.1, RM3.3.2
unnamed: D00_H135.1, RM3.4.2
unnamed: PWR_LED135.A, R22.2
PIN1/LCD_D00: GPIO_CON135.35, RM2.4.2, RM3.4.1, U1.2 (LCD_D00)
PIN2/LCD_D01: GPIO_CON135.33, RM2.3.2, RM3.3.1, U1.3 (LCD_D01)
PIN3/LCD_D02: GPIO_CON135.31, RM2.2.2, RM3.2.1, U1.4 (LCD_D02)
PIN4/LCD_D03: GPIO_CON135.29, RM2.1.2, RM3.1.1, U1.5 (LCD_D03)
PIN5/LCD_D04: GPIO_CON135.27, U1.6 (LCD_D04)
PIN6/LCD_D05: GPIO_CON135.25, R14.2, U1.7 (LCD_D05)
PIN7/LCD_D06: GPIO_CON135.23, U1.8 (LCD_D06)
PIN8/LCD_D07: GPIO_CON135.21, U1.9 (LCD_D07)
PIN9/LCD_D08/SSP2_MISO: GPIO_CON135.19, U1.22 (GPMI_D00/LCD_D08/SSP2_DATA0), UEXT135.7
PIN10/LCD_D09: GPIO_CON135.17, U1.23 (GPMI_D01/LCD_D09/SSP2_DATA1)
PIN11/LCD_D10: GPIO_CON135.15, U1.24 (GPMI_D02/LCD_D10/SSP2_DATA2)
PIN12/LCD_D11/UEXT_CS: GPIO_CON135.13, R13.1, U1.25 (GPMI_D03/LCD_D11/SSP2_DATA3), UEXT135.10
PIN13/LCD_D12: GPIO_CON135.11, U1.27 (GPMI_D04/LCD_D12/SSP2_DATA4)
PIN14/LCD_D13: GPIO_CON135.9, U1.26 (GPMI_D05/LCD_D13/SSP2_DATA5)
PIN15/LCD_D14: GPIO_CON135.7, U1.29 (GPMI_D06/LCD_D14/SSP2_DATA6)
PIN16/LCD_D15: GPIO_CON135.5, U1.28 (GPMI_D07/LCD_D15/SSP2_DATA7)
PIN17/LCD_D16: GPIO_CON135.3, U1.19 (GPMI_CLE/LCD_D16)
PIN18/LCD_D17/USB_EN: GPIO_CON135.4, R28.2, U1.20 (GPMI_ALE/LCD_D17), U3.4 (EN)
PIN19/LCD_DOTCLK: GPIO_CON135.6, U1.17 (LCD_DOTCK/GPMI_RDY3)
PIN20/LCD_VSYNC: GPIO_CON135.8, U1.16 (LCD_VSYNC/LCD_BUSY)
PIN21/LCD_HSYNC/I2C_SDA: GPIO_CON135.10, SDA_SW/SDA_HW135.1, U1.15 (LCD_HSYNC/I2C_SDA)
PIN22/LCD_EN/I2C_SCL: GPIO_CON135.12, SCL_SW/SCL_HW135.1, U1.11 (LCD_ENABLE/I2C_SCL)
PIN23/LCD_DISP: GPIO_CON135.14, U1.12 (LCD_RESET/GPMI_CE3N)
PIN24/LCD_WR: GPIO_CON135.16, U1.13 (LCD_WR)
PIN25/LCD_RS: GPIO_CON135.18, R15.2, U1.14 (LCD_RS)
PIN26/LCD_CS: GPIO_CON135.20, U1.10 (LCD_CS)
PIN27/PWM2: GPIO_CON135.22, U1.91 (PWM2/GPMI_RDY3)
PIN28/SOFT_SDA: GPIO_CON135.24, SDA_SW/SDA_HW135.3, U1.31 (GPMI_RDN)
PIN29/SOFT_SCL: GPIO_CON135.26, SCL_SW/SCL_HW135.3, U1.34 (GPMI_WPN)
PIN30: GPIO_CON135.28, U1.81 (GPMI_CE1N)
PIN31: GPIO_CON135.30, U1.82 (GPMI_CE0N)
PIN32/LRADC1: GPIO_CON135.32, U1.107 (LRADC1)
PIN33/LRADC0: GPIO_CON135.34, U1.108 (LRADC0)
PIN34/MIC: GPIO_CON135.36, U1.116 (MIC)
PSWITCH: R23.1, U1.119 (PSWITCH)
PWM0/DUART_RXD: R9.1, U1.125 (PWM0/ROTARYA/DUART_RX), U_DEBUG135.1
PWM1/DUART_TXD: U1.126 (PWM1/ROTARYB/DUART_TX), U_DEBUG135.2
RASN: U1.62 (EMI_RASN), U2.23 (#RAS)
RESET: R42.2, RESET135.2 (S)
SD_VCC: C29.2, C71.2, JTAG135.5, L6.2, SD135.4 (VDD)
SJTAG_PSW: PWR_BUT135.1, R23.2, R24.2, REC135.2, RM1.1.2 (2), SJTAG135.3
SSP1_CMD: JTAG135.6, R21.1, SD135.3 (CMD/DI), U1.83 (SSP1_CMD/SPI1_MOSI/JTAG_TDO)
SSP1_DATA0: JTAG135.2, RM1.3.1 (1), SD135.7 (DAT0/DO), U1.84 (SSP1_DATA0/SPI1_MISO/JTAG_TDI)
SSP1_DATA1: JTAG135.1, RM1.2.1 (1), SD135.8 (DAT1/RES), U1.85 (SSP1_DATA1/I2C_SCL/JTAG_TCLK)
SSP1_DATA2: JTAG135.8, RM1.4.1 (1), SD135.1 (DAT2/RES), U1.86 (SSP1_DATA2/I2C_SDA/JTAG_RTCK)
SSP1_DATA3: JTAG135.7, R20.1, SD135.2 (CD/DAT3/CS), U1.87 (SSP1_DATA3/SPI1_SS#/JTAG_TMS)
SSP1_SCK: JTAG135.4, SD135.5 (CLK/SCLK), U1.90 (SSP1_SCK/SPI1_SCK/JTAG_TRST)
SSP2_MOSI: U1.21 (GPMI_RDY1/SSP2_CMD), UEXT135.8
SSP2_SCK: U1.33 (GPMI_WRN/SSP2_SCK), UEXT135.9
TEST_PAD: T_P135.P$1, U1.32 (GPMI_RDY0/SSP2_DETECT)
USB_DM: PGM_FUSES135.1, U1.123 (USB_DM), U4.25 (DM0)
USB_DP: PGM_FUSES135.2, U1.124 (USB_DP), U4.26 (DP0)
V+: C5.2, C6.2, C7.2, C22.2, C30.2, C31.2, C32.2, C33.2, C34.2, C35.2, C36.2, C37.2, C38.1, R16.2, R18.2, U1.38 (VDDIO_EMIQ), U1.45 (VDDIO_EMI1), U1.53 (VDDIO_EMI2), U1.106 (VDDM/LRADC4), U2.1 (VDD1), U2.3 (VDDQ1), U2.9 (VDDQ2), U2.15 (VDDQ3), U2.18 (VDD2), U2.33 (VDD3), U2.55 (VDDQ4), U2.61 (VDDQ5)
VCC: 3.3VIO_E135.1, 3.3V_E135.2, C65.1, GPIO_CON135.38, PWR_SEL135.3, R11.2, R12.2, R13.2, SJTAG135.1, UEXT135.1
VDAC1: R26.1 (1.1), U1.104 (VDAC1)
VDD4P2: C9.2, C10.2, D1.K (C), U1.101 (VDD4P2)
VDDXTAL: C8.2, PWR_BUT135.2 (S), U1.120 (VDDXTAL)
VPP: 3.3VIO_E135.2, C3.2, C4.2, C15.2, C16.2, C60.1, D00_H135.2, D01_H135.2, D2.2 (K), D02_H135.2, D03_H135.2, L6.1, PWR_SEL135.1, R9.2, R15.1, R21.2, R25.2, RESET135.1, RM1.2.2 (2), RM1.3.2 (2), RM1.4.2 (2), U1.18 (VDDIO33_1), U1.92 (VDDIO33_3), U1.95 (DCDC_VDDIO)
WEN: U1.77 (EMI_WEN), U2.21 (#WE)
X1: C42.2, Q2.2, U4.6 (X1)
X2: C43.2, Q2.1, U4.7 (X2)
XTALI: C23.2, Q1.2, T2.3 (C), U1.122 (XTALI)
XTALO: C24.2, Q1.1, T1.3 (C), U1.121 (XTALO)

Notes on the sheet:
POWER SUPPLY CIRCUIT
Headphones resistance Rl = Rr = 16 Ohms!
LI-ION_BATTERY
Place T1 and T2 as close as
possible to Q1
Reset Circuit
512Mb DDR SDRAM (32Mx16)
MicroSD
Composite Video
Headphones and Line-In
POWER/REC Button
BOOT MODE SELECT
UEXT
BOOT MODE SELECT:
LCD DATA
BOOT MODE
D03
D02
D01
D00
USB
3.3V I2C Master
3.3V SPI Flash 1 Master
3.3V SPI Flash 2 Master
3.3V NAND
Startup waits for JTAG debugger connection
3.3V SD/MMC 1 (Default !!!)
3.3V SD/MMC 2
LCD_RS must to be pulled
High to enable Resistor Boot Mode.
If pulled low, the i.MX233 will
attempt to boot from OTP.
LCD_D05 is ETM Enable Bit:
IF Low -> ETM disabled
IF High -> ETM enabled
GPIO
Debug: UART or SJTAG
USB-HOSTs
VCC
GND
